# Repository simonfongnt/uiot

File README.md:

# Universal Internet of Things (IoT)
This project introduces an easy and cost-effective IoT platform.

The devices speaks to the Webserver (for OTA purpose) and the PC (for remote control) via LAN
...

Basic knowledge of PCB design and coding is perferred. 

| Example       | Required      | Output Files  | Usage                      |
| ------------- | ------------- | ------------- | -------------------------- |
| PCB Design    | KiCad         | Gerber        | Order PCB                  |
| Firmware      | Arduino IDE   | .ino          | flash ESP-12 uC            |
| Web Server    | any notepad   | .php          | OTA purpose                |
| PC Software   | Pyhton 3.X    | .py           | console purpose            |
| ...           |               |               |                            |
| ...           |               |               |                            |

To initiate this project, An set of PCB example and code example for specific device are provided for reference.

## Updates:

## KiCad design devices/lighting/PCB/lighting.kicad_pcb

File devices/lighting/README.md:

# Universal Internet of Things (IoT)

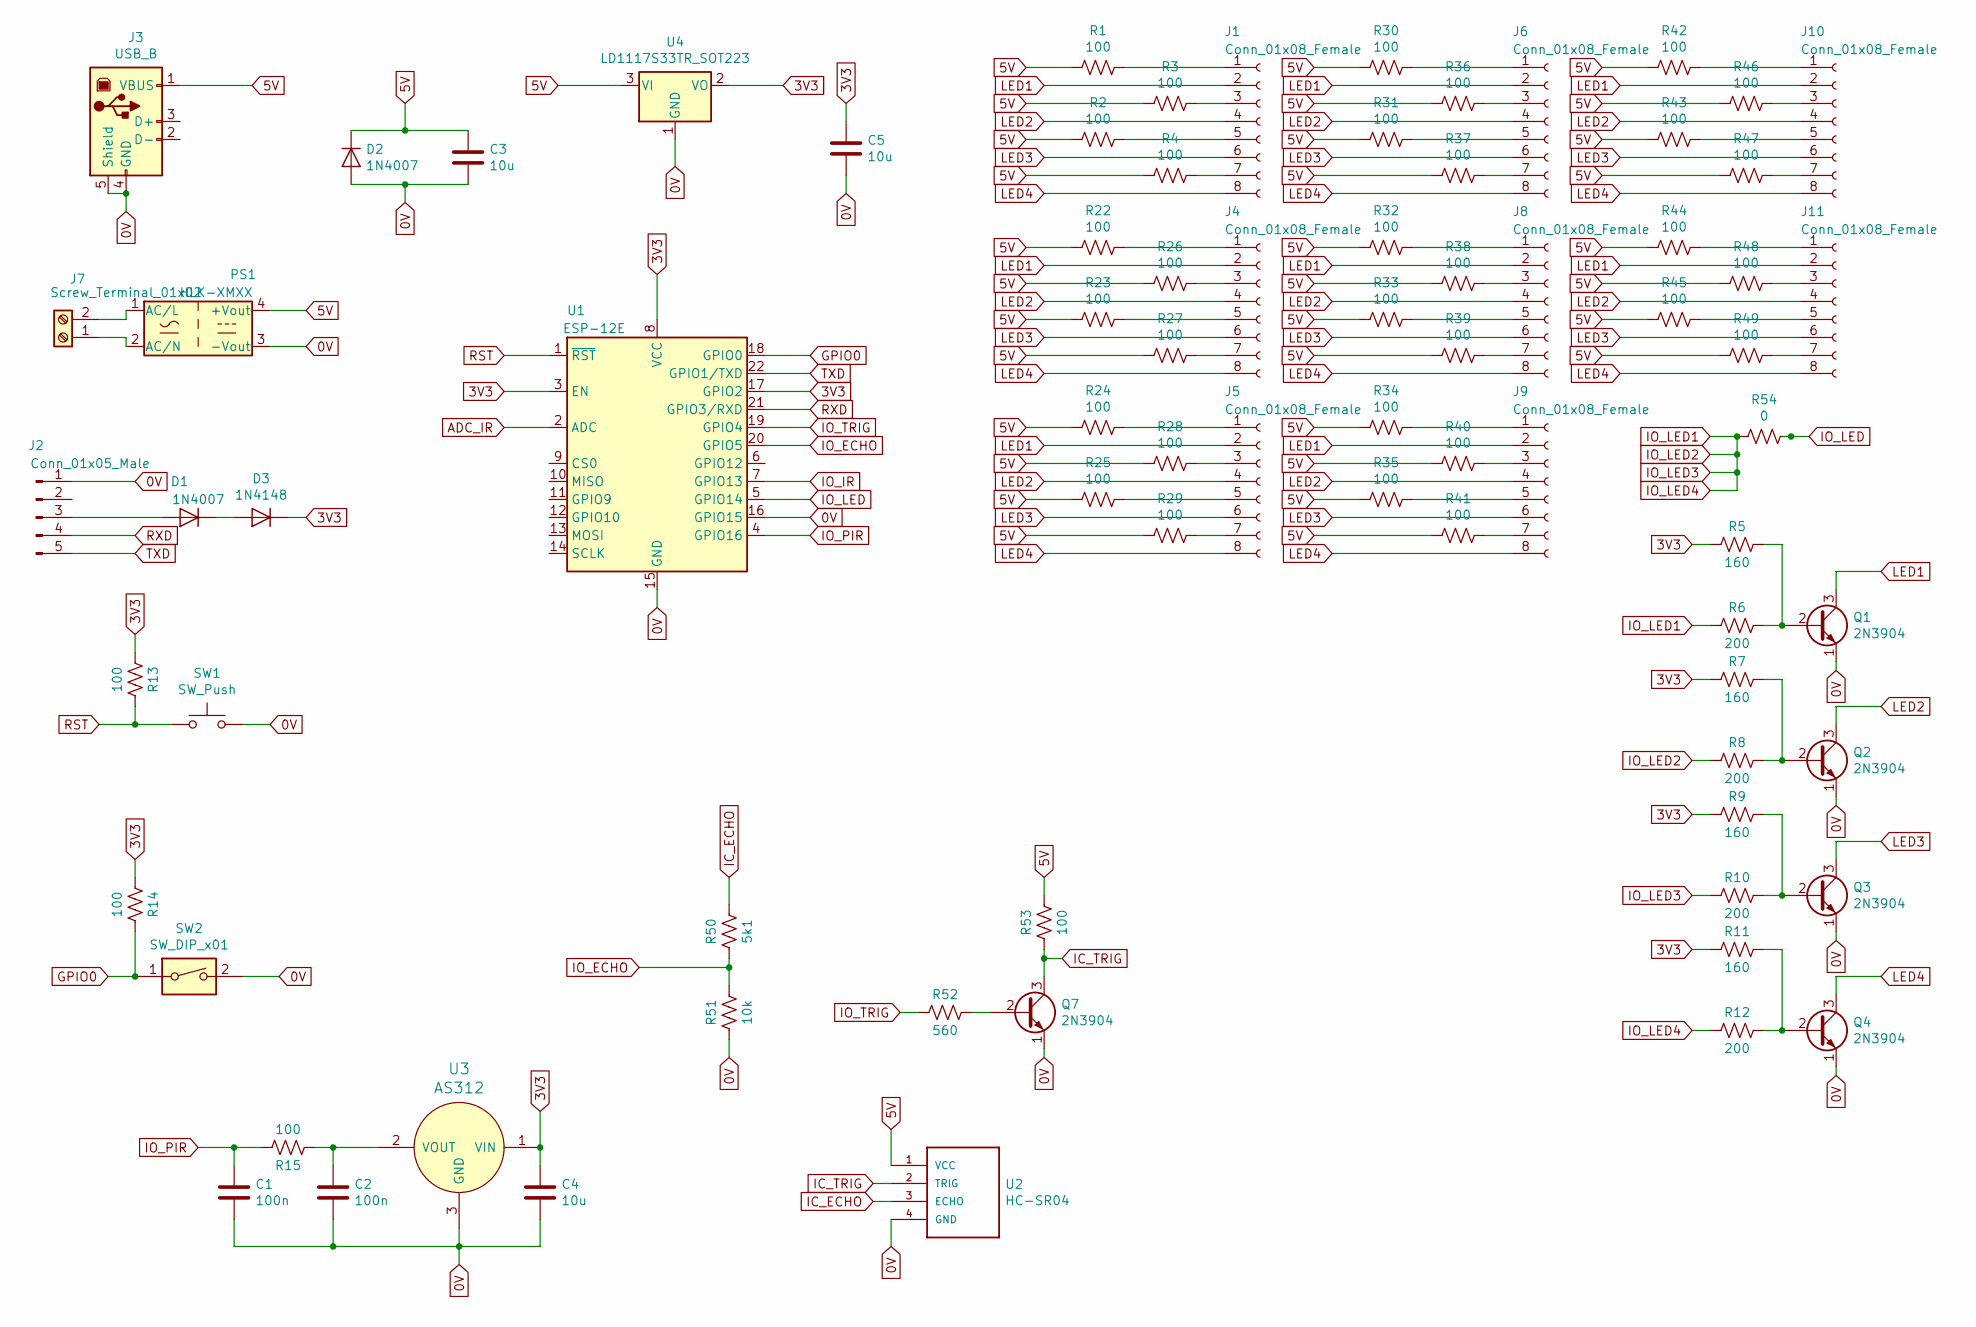
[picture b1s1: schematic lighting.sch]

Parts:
C1, C2: 100n; C_0805_2012Metric_Pad1.15x1.40mm_HandSolder
C3, C4, C5: 10u; C_0805_2012Metric_Pad1.15x1.40mm_HandSolder
D1, D2: 1N4007; D_DO-41_SOD81_P10.16mm_Horizontal
D3: 1N4148; D_DO-35_SOD27_P7.62mm_Horizontal
J1, J4, J5, J6, J8, J9, J10, J11: Conn_01x08_Female; PinHeader_1x08_P2.54mm_Vertical
J2: Conn_01x05_Male; PinHeader_1x05_P2.54mm_Vertical
J3: USB_B; USB_B_OST_USB-B1HSxx_Horizontal
J7: Screw_Terminal_01x02; TerminalBlock_MetzConnect_Type171_RT13702HBWC_1x02_P7.50mm_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
PS1: HLK-XMXX
Q1, Q2, Q3, Q4, Q7: 2N3904; TO-92_Inline
R1, R2, R3, R4, R13, R14, R15, R22, R23, R24, R25, R26, R27, R28, R29, R30, R31, R32, R33, R34, R35, R36, R37, R38, R39, R40, R41, R42, R43, R44, R45, R46, R47, R48, R49, R53: 100; R_0805_2012Metric_Pad1.15x1.40mm_HandSolder
R5, R7, R9, R11: 160; R_0805_2012Metric_Pad1.15x1.40mm_HandSolder
R6, R8, R10, R12: 200; R_0805_2012Metric_Pad1.15x1.40mm_HandSolder
R50: 5k1; R_0805_2012Metric_Pad1.15x1.40mm_HandSolder
R51: 10k; R_0805_2012Metric_Pad1.15x1.40mm_HandSolder
R52: 560; R_0805_2012Metric_Pad1.15x1.40mm_HandSolder
R54: 0; R_0805_2012Metric_Pad1.15x1.40mm_HandSolder
SW1: SW_Push; SW_PUSH_6mm_H4.3mm
SW2: SW_DIP_x01; SW_DIP_SPSTx01_Slide_9.78x4.72mm_W7.62mm_P2.54mm
U1: ESP-12E
U2: HC-SR04; XCVR_HC-SR04
U3: AS312
U4: LD1117S33TR_SOT223; SOT-223-3_TabPin2

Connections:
0V: C1.2, C2.2, C3.2, C4.2, C5.2, D2.2 (A), J2.1, J3.4 (GND), J3.5 (Shield), PS1.3 (-Vout), Q1.1 (E), Q2.1 (E), Q3.1 (E), Q4.1 (E), Q7.1 (E), R51.2, SW1.2, SW2.2, U1.15 (GND), U1.16 (GPIO15), U2.4 (GND), U3.3 (GND), U4.1 (GND)
3V3: C4.1, C5.1, D3.1 (K), R5.2, R7.2, R9.2, R11.2, R13.2, R14.2, U1.3 (EN), U1.8 (VCC), U1.17 (GPIO2), U3.1 (VIN), U4.2 (VO)
5V: C3.1, D2.1 (K), J3.1 (VBUS), PS1.4 (+Vout), R1.2, R2.2, R3.2, R4.2, R22.2, R23.2, R24.2, R25.2, R26.2, R27.2, R28.2, R29.2, R30.2, R31.2, R32.2, R33.2, R34.2, R35.2, R36.2, R37.2, R38.2, R39.2, R40.2, R41.2, R42.2, R43.2, R44.2, R45.2, R46.2, R47.2, R48.2, R49.2, R53.1, U2.1 (VCC), U4.3 (VI)
ADC_IR: U1.2 (ADC)
GPIO0: R14.1, SW2.1, U1.18 (GPIO0)
IC_ECHO: R50.1, U2.3 (ECHO)
IC_TRIG: Q7.3 (C), R53.2, U2.2 (TRIG)
IO_ECHO: R50.2, R51.1, U1.20 (GPIO5)
IO_IR: U1.7 (GPIO13)
IO_LED: R54.1, U1.5 (GPIO14)
IO_LED1: R6.2, R8.2, R10.2, R12.2, R54.2
IO_PIR: C1.1, R15.1, U1.4 (GPIO16)
IO_TRIG: R52.2, U1.19 (GPIO4)
LED1: J1.2, J4.2, J5.2, J6.2, J8.2, J9.2, J10.2, J11.2, Q1.3 (C)
LED2: J1.4, J4.4, J5.4, J6.4, J8.4, J9.4, J10.4, J11.4, Q2.3 (C)
LED3: J1.6, J4.6, J5.6, J6.6, J8.6, J9.6, J10.6, J11.6, Q3.3 (C)
LED4: J1.8, J4.8, J5.8, J6.8, J8.8, J9.8, J10.8, J11.8, Q4.3 (C)
unnamed: C2.1, R15.2, U3.2 (VOUT)
unnamed: D1.1 (K), D3.2 (A)
unnamed: D1.2 (A), J2.3
unnamed: J1.1, R1.1
unnamed: J1.3, R3.1
unnamed: J1.5, R2.1
unnamed: J1.7, R4.1
unnamed: J4.1, R22.1
unnamed: J4.3, R26.1
unnamed: J4.5, R23.1
unnamed: J4.7, R27.1
unnamed: J5.1, R24.1
unnamed: J5.3, R28.1
unnamed: J5.5, R25.1
unnamed: J5.7, R29.1
unnamed: J6.1, R30.1
unnamed: J6.3, R36.1
unnamed: J6.5, R31.1
unnamed: J6.7, R37.1
unnamed: J7.1, PS1.2 (AC/N)
unnamed: J7.2, PS1.1 (AC/L)
unnamed: J8.1, R32.1
unnamed: J8.3, R38.1
unnamed: J8.5, R33.1
unnamed: J8.7, R39.1
unnamed: J9.1, R34.1
unnamed: J9.3, R40.1
unnamed: J9.5, R35.1
unnamed: J9.7, R41.1
unnamed: J10.1, R42.1
unnamed: J10.3, R46.1
unnamed: J10.5, R43.1
unnamed: J10.7, R47.1
unnamed: J11.1, R44.1
unnamed: J11.3, R48.1
unnamed: J11.5, R45.1
unnamed: J11.7, R49.1
unnamed: Q1.2 (B), R5.1, R6.1
unnamed: Q2.2 (B), R7.1, R8.1
unnamed: Q3.2 (B), R9.1, R10.1
unnamed: Q4.2 (B), R11.1, R12.1
unnamed: Q7.2 (B), R52.1
RST: R13.1, SW1.1, U1.1 (~RST)
RXD: J2.4, U1.21 (GPIO3/RXD)
TXD: J2.5, U1.22 (GPIO1/TXD)

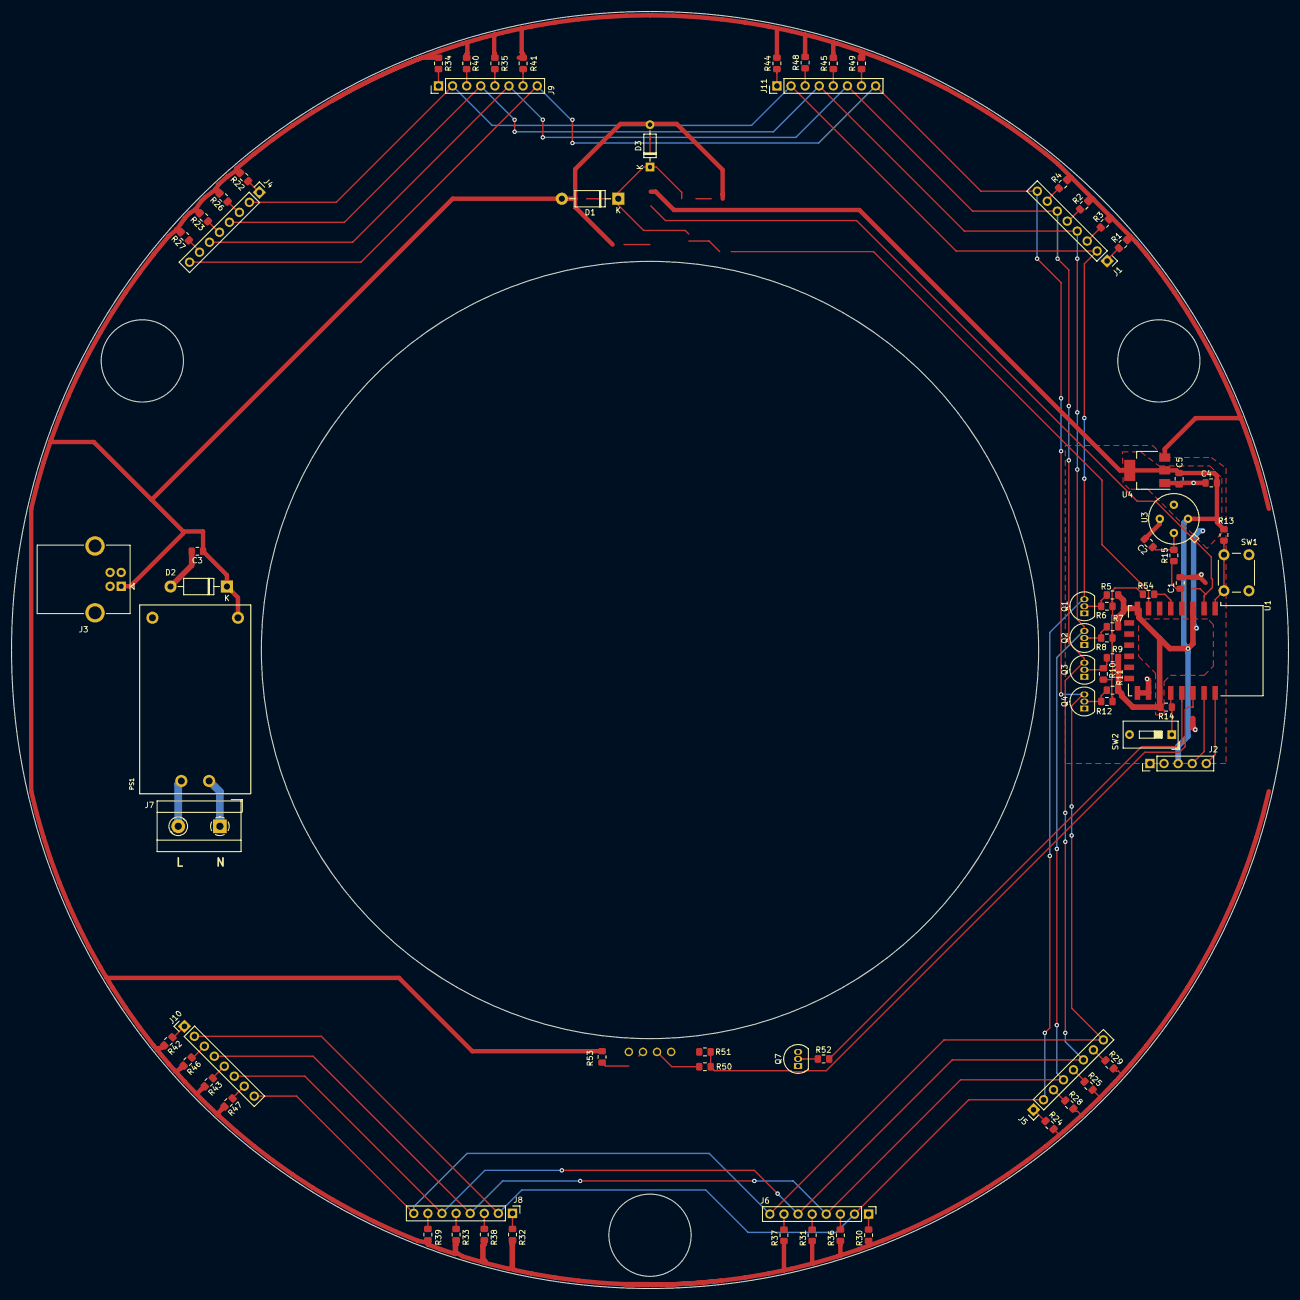
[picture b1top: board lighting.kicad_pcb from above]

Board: 2 copper layers, 230.0 x 230.0 mm, 79 parts (1 on the bottom side), 60 nets.

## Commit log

2019-01-03 Set theme jekyll-theme-midnight
2019-01-11 Initialize files
2019-01-11 adding picture
2019-01-22 Edited README via new pc
